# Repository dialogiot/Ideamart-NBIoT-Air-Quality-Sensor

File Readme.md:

##  Ideamart NB-IoT Air Quality Sensor

The board is developed based on the SIM7000C and SIM7000E Modules as well as the Microcontroller ATMega 328 based on the most popular Arduino UNO PIN layout. Therefore this board is compatible with any shield that is compatible with the Arduino UNO

* Temperature(Celsius)
* Carbon Dioxide(ppm)
* Pressure(Pa)
* Humidity(%)
* Ammonia(ppm)
* Butane(ppm)
* Carbon Monoxide(ppm)
* Ethanol(ppm)
* Hydrogen(ppm)
* Methane(ppm)
* Nitrogen Dioxide(ppm)
* Propane(ppm)
* Latitude, Longitude
* Altitude(m)
* MSL Altitude(m)
* Speed Over Ground(km/h)
* Course Over Ground(degrees)
* RSSI
* Battery Level(%)
* UTC date & Time
* Volatile Organic Compound(ppb)

More  (https://idealab.ideamart.io/EnvSensor/)

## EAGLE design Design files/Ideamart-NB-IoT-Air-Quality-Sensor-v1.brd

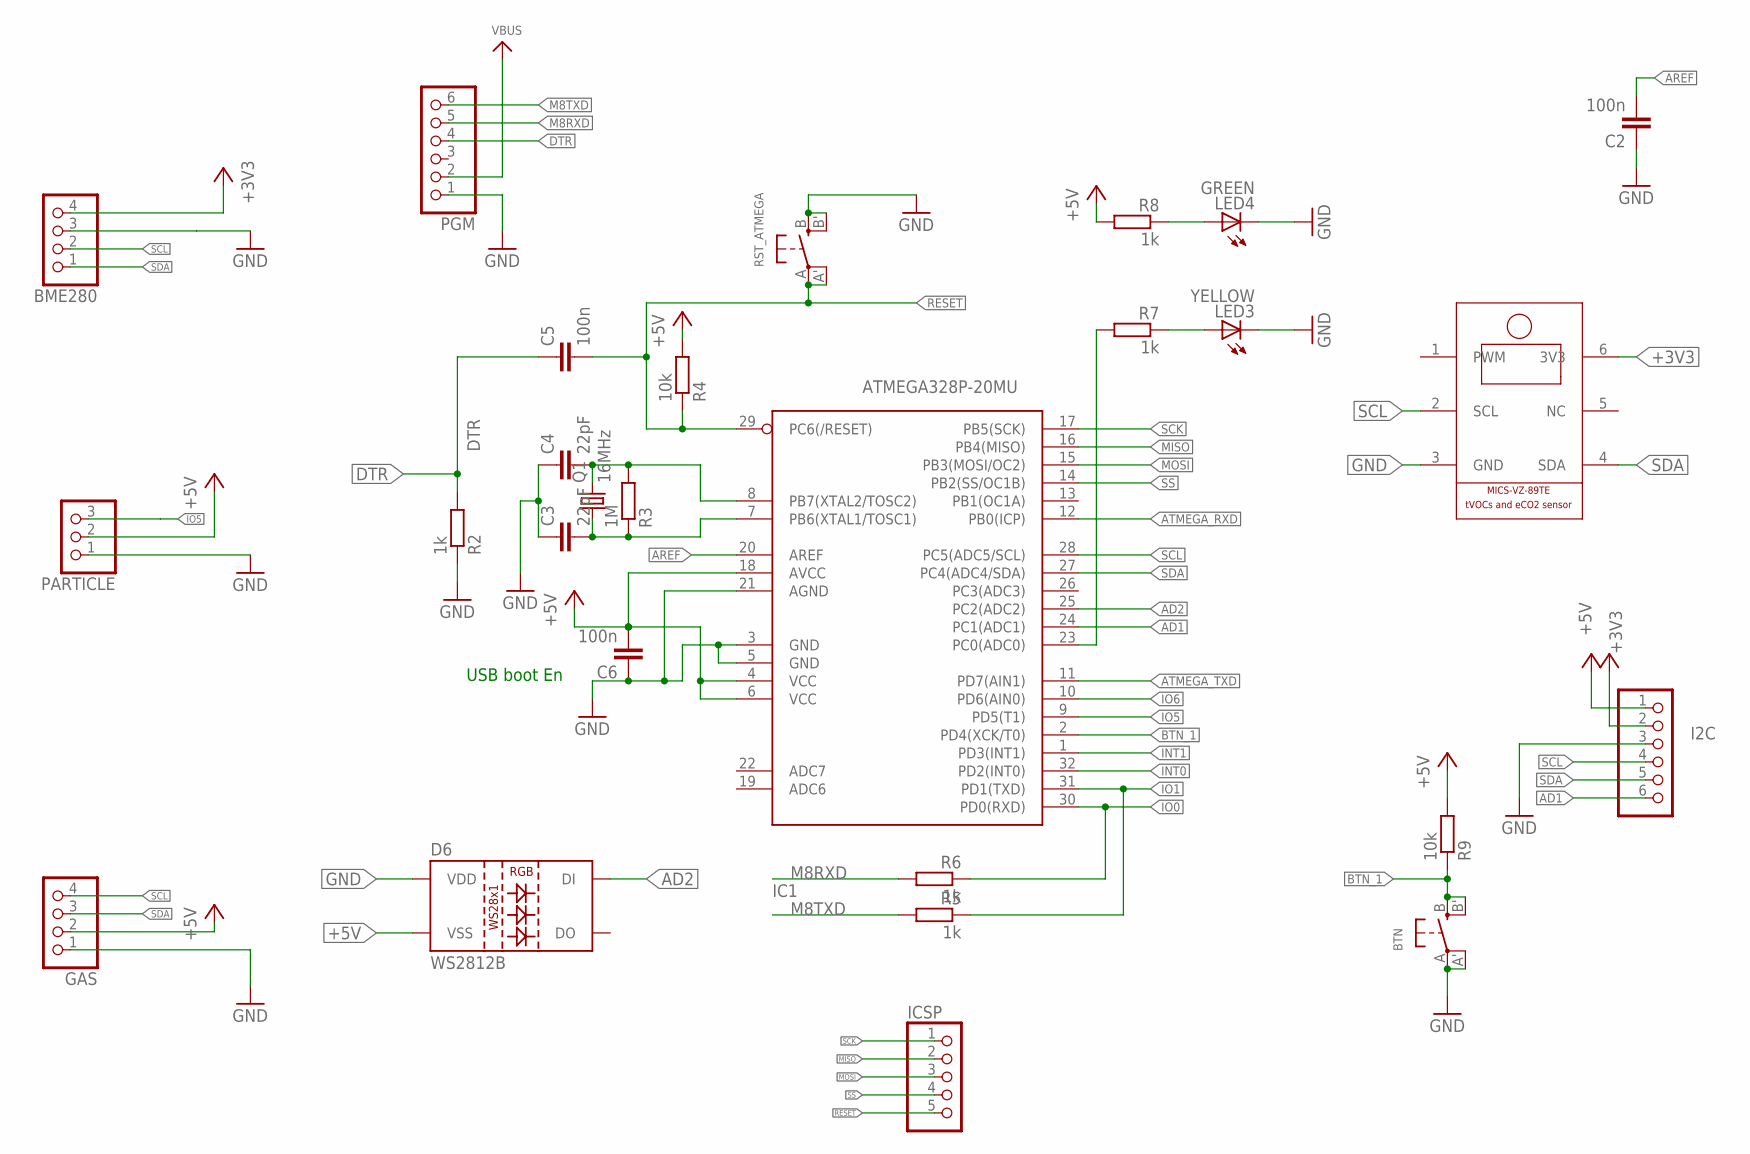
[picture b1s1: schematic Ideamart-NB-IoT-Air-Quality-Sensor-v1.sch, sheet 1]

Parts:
BME280: PINHD-1X4; 1X04
BTN: SWITCH_TACT_SMT4.6X2.8; BTN_KMR2_4.6X2.8
C2, C5, C6: 100n; C0805
C3, C4: 22pF; C0805
D6: WS2812B
GAS: PINHD-1X4; 1X04
I2C: PINHD-1X6; 1X06
IC1: ATMEGA328P-20MU; TQFP32-08
ICSP: PINHD-1X5; 1X05
LED3: YELLOW; CHIP-LED0805
LED4: GREEN; CHIP-LED0805
PARTICLE: PINHD-1X3; 1X03
PGM: PINHD-1X6; 1X06
Q1: 16MHz; CTS406
R2, R5, R6, R7, R8: 1k; R0805
R3: 1M; R0805
R4, R9: 10k; R0805
RST_ATMEGA: SWITCH_TACT_SMT4.6X2.8; BTN_KMR2_4.6X2.8
U$1: MICS-VZ-89TE

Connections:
+3V3: BME280.4, I2C.2, U$1.6 (3V3); also elsewhere on the board
+5V: C6.2, D6.3 (VSS), GAS.2, I2C.1, IC1.4 (VCC), IC1.6 (VCC), IC1.18 (AVCC), PARTICLE.2, R4.2, R8.2, R9.2; also elsewhere on the board
AD1: I2C.6, IC1.24 (PC1(ADC1))
AD2: D6.4 (DI), IC1.25 (PC2(ADC2))
AREF: C2.2, IC1.20 (AREF)
ATMEGA_RXD: IC1.12 (PB0(ICP)); also elsewhere on the board
ATMEGA_TXD: IC1.11 (PD7(AIN1)); also elsewhere on the board
BTN_1: BTN.B (S), BTN.B' (S1), IC1.2 (PD4(XCK/T0)), R9.1
DTR: C5.1, PGM.4, R2.2
GND: BME280.3, BTN.A, BTN.A' (P1), C2.1, C3.1, C4.1, C6.1, D6.1 (VDD), GAS.1, I2C.3, IC1.3 (GND), IC1.5 (GND), IC1.21 (AGND), LED3.C, LED4.C, PARTICLE.1, PGM.1, R2.1, RST_ATMEGA.B (S), RST_ATMEGA.B' (S1), U$1.3 (GND); also elsewhere on the board
INT0: IC1.32 (PD2(INT0))
INT1: IC1.1 (PD3(INT1))
IO0: IC1.30 (PD0(RXD)), R6.1
IO1: IC1.31 (PD1(TXD)), R5.1
IO5: IC1.9 (PD5(T1)), PARTICLE.3
IO6: IC1.10 (PD6(AIN0))
M8RXD: PGM.5, R6.2
M8TXD: PGM.6, R5.2
MISO: IC1.16 (PB4(MISO)), ICSP.2
MOSI: IC1.15 (PB3(MOSI/OC2)), ICSP.3; also elsewhere on the board
unnamed: LED3.A, R7.1
unnamed: LED4.A, R8.1
unnamed: IC1.23 (PC0(ADC0)), R7.2
RESET: C5.2, IC1.29 (PC6(/RESET)), ICSP.5, R4.1, RST_ATMEGA.A, RST_ATMEGA.A' (P1)
SCK: IC1.17 (PB5(SCK)), ICSP.1; also elsewhere on the board
SCL: BME280.2, GAS.4, I2C.4, IC1.28 (PC5(ADC5/SCL)), U$1.2 (SCL)
SDA: BME280.1, GAS.3, I2C.5, IC1.27 (PC4(ADC4/SDA)), U$1.4 (SDA)
SS: IC1.14 (PB2(SS/OC1B)), ICSP.4
VBUS: PGM.2; also elsewhere on the board
XTAL1: C3.2, IC1.7 (PB6(XTAL1/TOSC1)), Q1.1, R3.1
XTAL2: C4.2, IC1.8 (PB7(XTAL2/TOSC2)), Q1.3 (2), R3.2

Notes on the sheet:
USB boot En

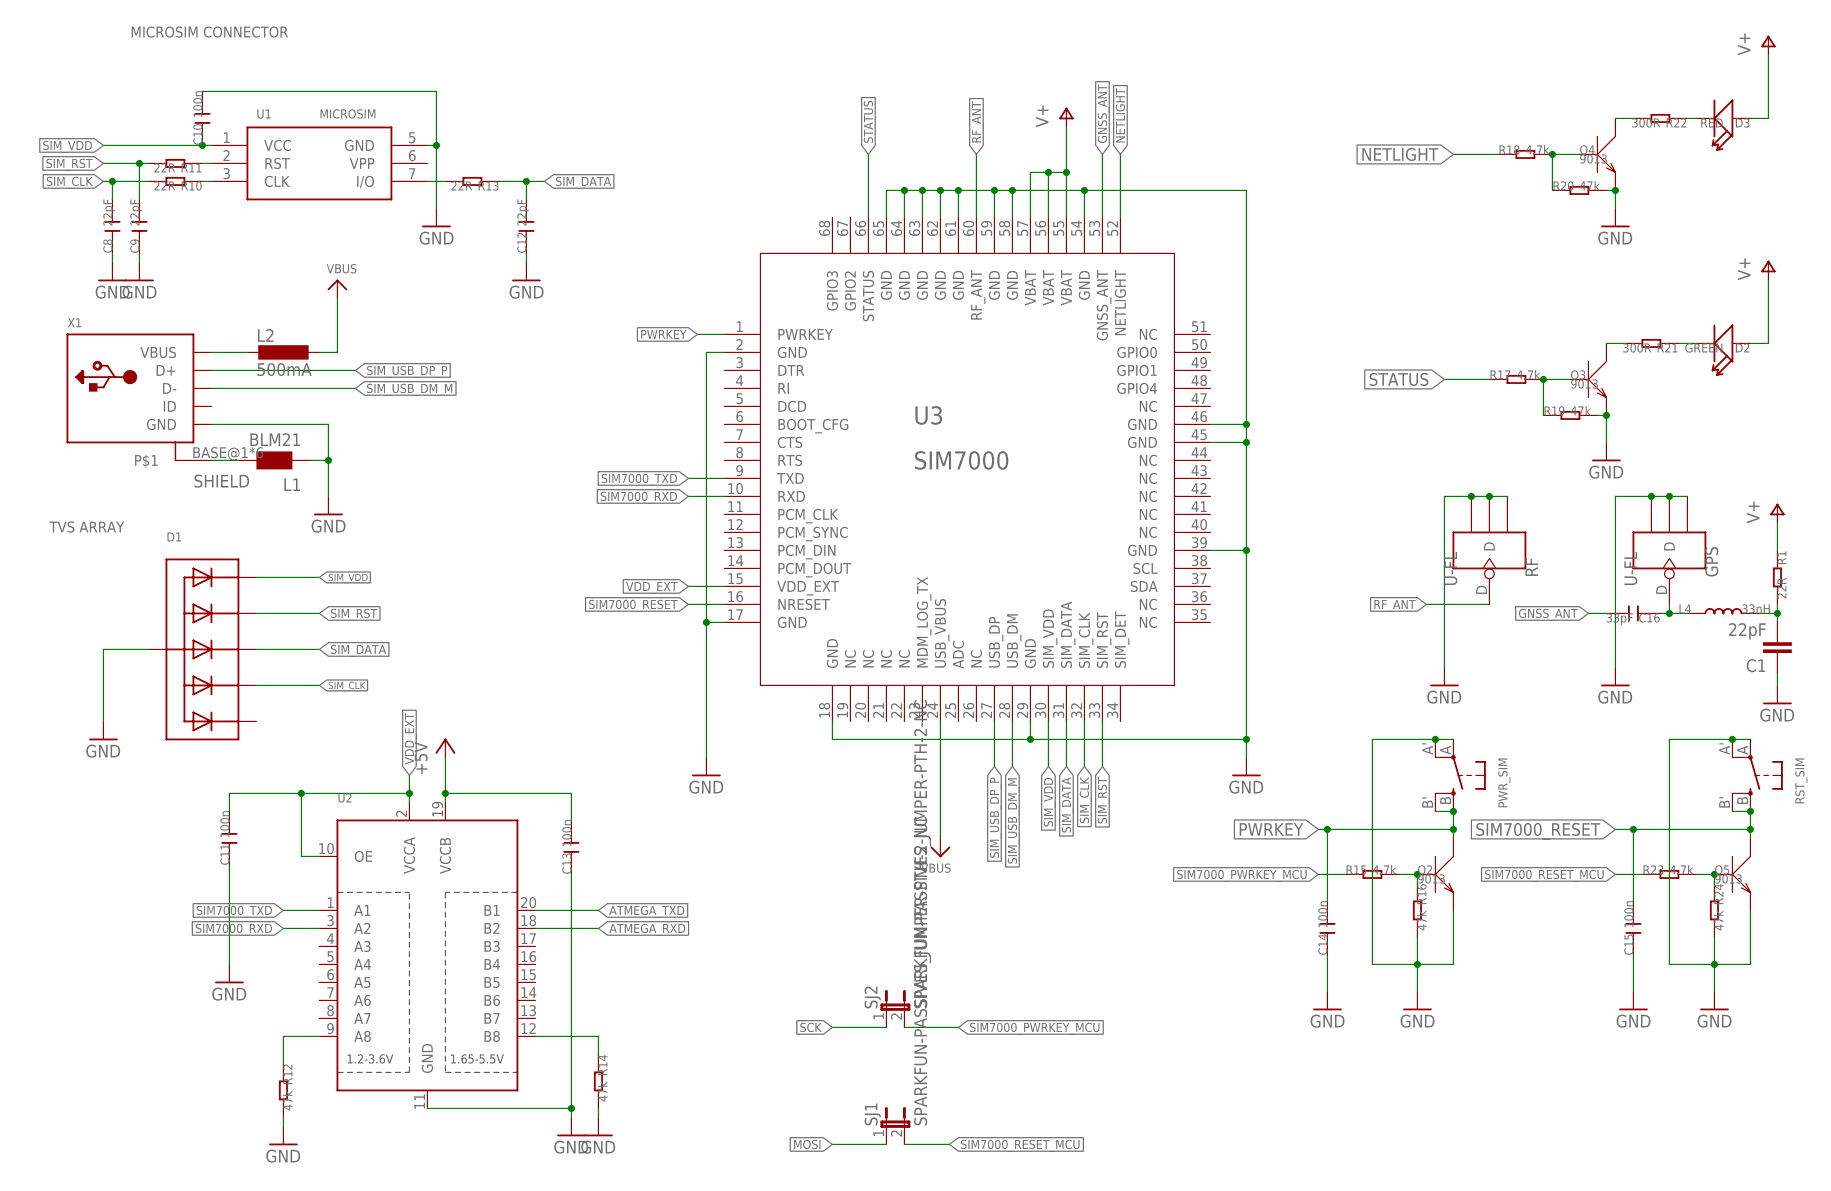
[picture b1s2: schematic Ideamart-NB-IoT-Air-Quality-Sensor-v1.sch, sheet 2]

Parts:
C1: 22pF; C0805
C8, C9, C12: 22pF; 0805
C10, C11, C13, C14, C15: 100n; 0805
C16: 33pF; 0805
D1: TVSARRAY_5LANE; SOT363
D2: GREEN; LED-0805
D3: RED; LED-0805
GPS: U-FL; 4P-U-FL
L1: BLM21; 0805
L2: 500mA; L1812
L4: 33nH; L0805
PWR_SIM: SWITCH_TACT_SMT4.6X2.8; BTN_KMR2_4.6X2.8
Q2, Q3, Q4, Q5: 9013; SOT23
R1, R10, R11, R13: 22R; 0805
R12, R14, R16, R19, R20, R24: 47k; 0805
R15, R17, R18, R23: 4.7k; 0805
R21, R22: 300R; 0805
RF: U-FL; 4P-U-FL
RST_SIM: SWITCH_TACT_SMT4.6X2.8; BTN_KMR2_4.6X2.8
SJ1, SJ2: SPARKFUN-PASSIVES_JUMPER-PTH-2-NC; SPARKFUN-PASSIVES_PTH-JUMPER-NC_BOTTOM_NO_SILK
U1: MICROSIM
U2: TXB0108PWR; TSSOP20
U3: SIM7000
X1: USB_MICRO_20329_V2; 4UCONN_20329_V2

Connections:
+5V: C13.2, U2.19 (VCCB); also elsewhere on the board
ATMEGA_RXD: U2.18 (B2); also elsewhere on the board
ATMEGA_TXD: U2.20 (B1); also elsewhere on the board
GND: C1.1, C8.1, C9.1, C10.2, C11.1, C12.1, C13.1, C14.1, C15.1, D1.2 (A), GPS.GND1, GPS.GND2, GPS.GND3, L1.1, PWR_SIM.A, PWR_SIM.A' (P1), Q2.2 (E), Q3.2 (E), Q4.2 (E), Q5.2 (E), R12.2, R14.2, R16.2, R19.2, R20.2, R24.2, RF.GND1, RF.GND2, RF.GND3, RST_SIM.A, RST_SIM.A' (P1), U1.5 (GND), U2.11 (GND), U3.2 (GND), U3.17 (GND), U3.18 (GND), U3.29 (GND), U3.39 (GND), U3.45 (GND), U3.46 (GND), U3.54 (GND), U3.58 (GND), U3.59 (GND), U3.61 (GND), U3.62 (GND), U3.63 (GND), U3.64 (GND), U3.65 (GND), X1.GND; also elsewhere on the board
GNSS_ANT: C16.2, U3.53 (GNSS_ANT)
GPIO2: U3.67 (GPIO2)
GPIO3: U3.68 (GPIO3)
MOSI: SJ1.1; also elsewhere on the board
unnamed: Q3.3 (C), R21.2
unnamed: D2.-, R21.1
unnamed: Q3.1 (B), R17.2, R19.1
unnamed: R13.2, U1.7 (I/O)
unnamed: R10.1, U1.3 (CLK)
unnamed: R11.1, U1.2 (RST)
unnamed: Q5.1 (B), R23.2, R24.1
unnamed: L2.2, X1.VBUS
unnamed: Q4.3 (C), R22.2
unnamed: D3.-, R22.1
unnamed: Q4.1 (B), R18.2, R20.1
unnamed: C16.1, GPS.D, L4.1
unnamed: R12.1, U2.9 (A8)
unnamed: R14.1, U2.12 (B8)
unnamed: C1.2, L4.2, R1.2
unnamed: Q2.1 (B), R15.2, R16.1
NETLIGHT: R18.1, U3.52 (NETLIGHT)
PWRKEY: C14.2, PWR_SIM.B (S), PWR_SIM.B' (S1), Q2.3 (C), U3.1 (PWRKEY)
RF_ANT: RF.D, U3.60 (RF_ANT)
SCK: SJ2.1; also elsewhere on the board
SHIELD: L1.2, X1.BASE@1, X1.BASE@2, X1.SPRT@1, X1.SPRT@2, X1.SPRT@3, X1.SPRT@4
SIM7000_PWRKEY_MCU: R15.1, SJ2.2
SIM7000_RESET: C15.2, Q5.3 (C), RST_SIM.B (S), RST_SIM.B' (S1), U3.16 (NRESET)
SIM7000_RESET_MCU: R23.1, SJ1.2
SIM7000_RXD: U2.3 (A2), U3.10 (RXD)
SIM7000_TXD: U2.1 (A1), U3.9 (TXD)
SIM_CLK: C8.2, D1.5 (C4), R10.2, U3.32 (SIM_CLK)
SIM_DATA: C12.2, D1.4 (C3), R13.1, U3.31 (SIM_DATA)
SIM_RST: C9.2, D1.3 (C2), R11.2, U3.33 (SIM_RST)
SIM_USB_DM_M: U3.28 (USB_DM), X1.D-
SIM_USB_DP_P: U3.27 (USB_DP), X1.D+
SIM_VDD: C10.1, D1.1 (C1), U1.1 (VCC), U3.30 (SIM_VDD)
STATUS: R17.1, U3.66 (STATUS)
V+: D2.+, D3.+, R1.1, U3.55 (VBAT), U3.56 (VBAT), U3.57 (VBAT); also elsewhere on the board
VBUS: L2.1, U3.24 (USB_VBUS); also elsewhere on the board
VDD_EXT: C11.2, U2.2 (VCCA), U2.10 (OE), U3.15 (VDD_EXT)

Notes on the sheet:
TVS ARRAY
MICROSIM CONNECTOR

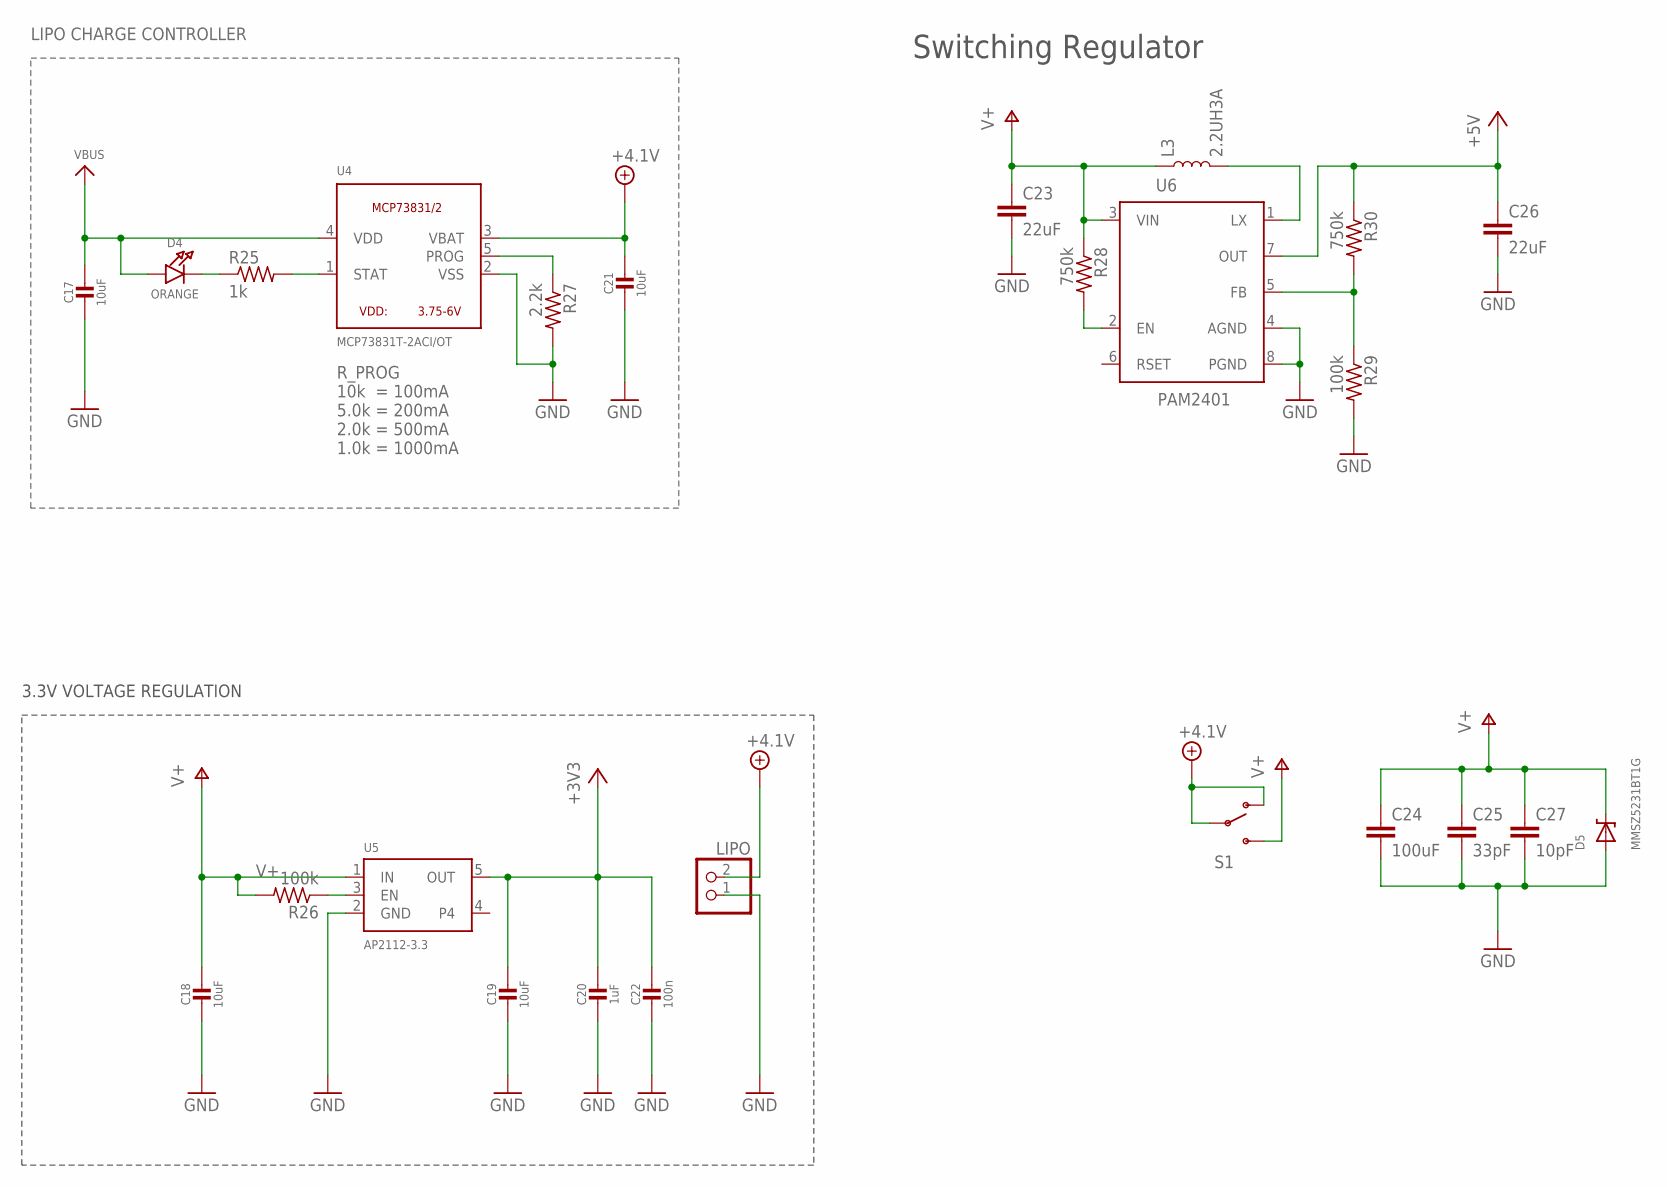
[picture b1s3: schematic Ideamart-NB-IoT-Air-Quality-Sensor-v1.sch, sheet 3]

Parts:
C17, C21: 10uF; _0805
C18, C19: 10uF; _0805MP
C20: 1uF; _0805MP
C22: 100n; _0805MP
C23, C26: 22uF; 0805
C24: 100uF; 1210
C25: 33pF; 0805
C27: 10pF; 0805
D4: ORANGE; CHIPLED_0805
D5: MMSZ5231BT1G; SOD-123
L3: 2.2UH3A; INDUCTOR_4X4MM
LIPO: JST_2PIN-SMT; JST-PH-2-SMT
R25: 1k; M0805
R26, R29: 100k; M0805
R27: 2.2k; M0805
R28, R30: 750k; M0805
S1: SWITCH-SPDT-SMD-A; SWITCH-SPST-SMD-A
U4: MCP73831T-2ACI/OT; SOT23-5
U5: AP2112-3.3; SOT23-5
U6: PAM2401; MSOP8

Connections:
+3V3: C19.1, C20.1, C22.1, U5.5 (OUT); also elsewhere on the board
+4.1V: C21.1, LIPO.2 (1), S1.1 (O), S1.2, U4.3 (VBAT)
+5V: C26.1, R30.1, U6.7 (OUT); also elsewhere on the board
EN: R28.2, U6.2 (EN)
GND: C17.2, C18.2, C19.2, C20.2, C21.2, C22.2, C23.2, C24.2, C25.2, C26.2, C27.2, D5.A, LIPO.1 (2), R27.2, R29.2, U4.2 (VSS), U5.2 (GND), U6.4 (AGND), U6.8 (PGND); also elsewhere on the board
unnamed: R26.1, U5.3 (EN)
unnamed: D4.C, R25.1
unnamed: R25.2, U4.1 (STAT)
unnamed: R27.1, U4.5 (PROG)
unnamed: R29.1, R30.2, U6.5 (FB)
unnamed: L3.P$2 (2), U6.1 (LX)
V+: C18.1, C23.1, C24.1, C25.1, C27.1, D5.C, L3.P$1 (1), R26.2, R28.1, S1.3 (S), U5.1 (IN), U6.3 (VIN); also elsewhere on the board
VBUS: C17.1, D4.A, U4.4 (VDD); also elsewhere on the board

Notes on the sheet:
3.3V VOLTAGE REGULATION
R_PROG 10k = 100mA 5.0k = 200mA 2.0k = 500mA 1.0k = 1000mA
LIPO CHARGE CONTROLLER
Switching Regulator

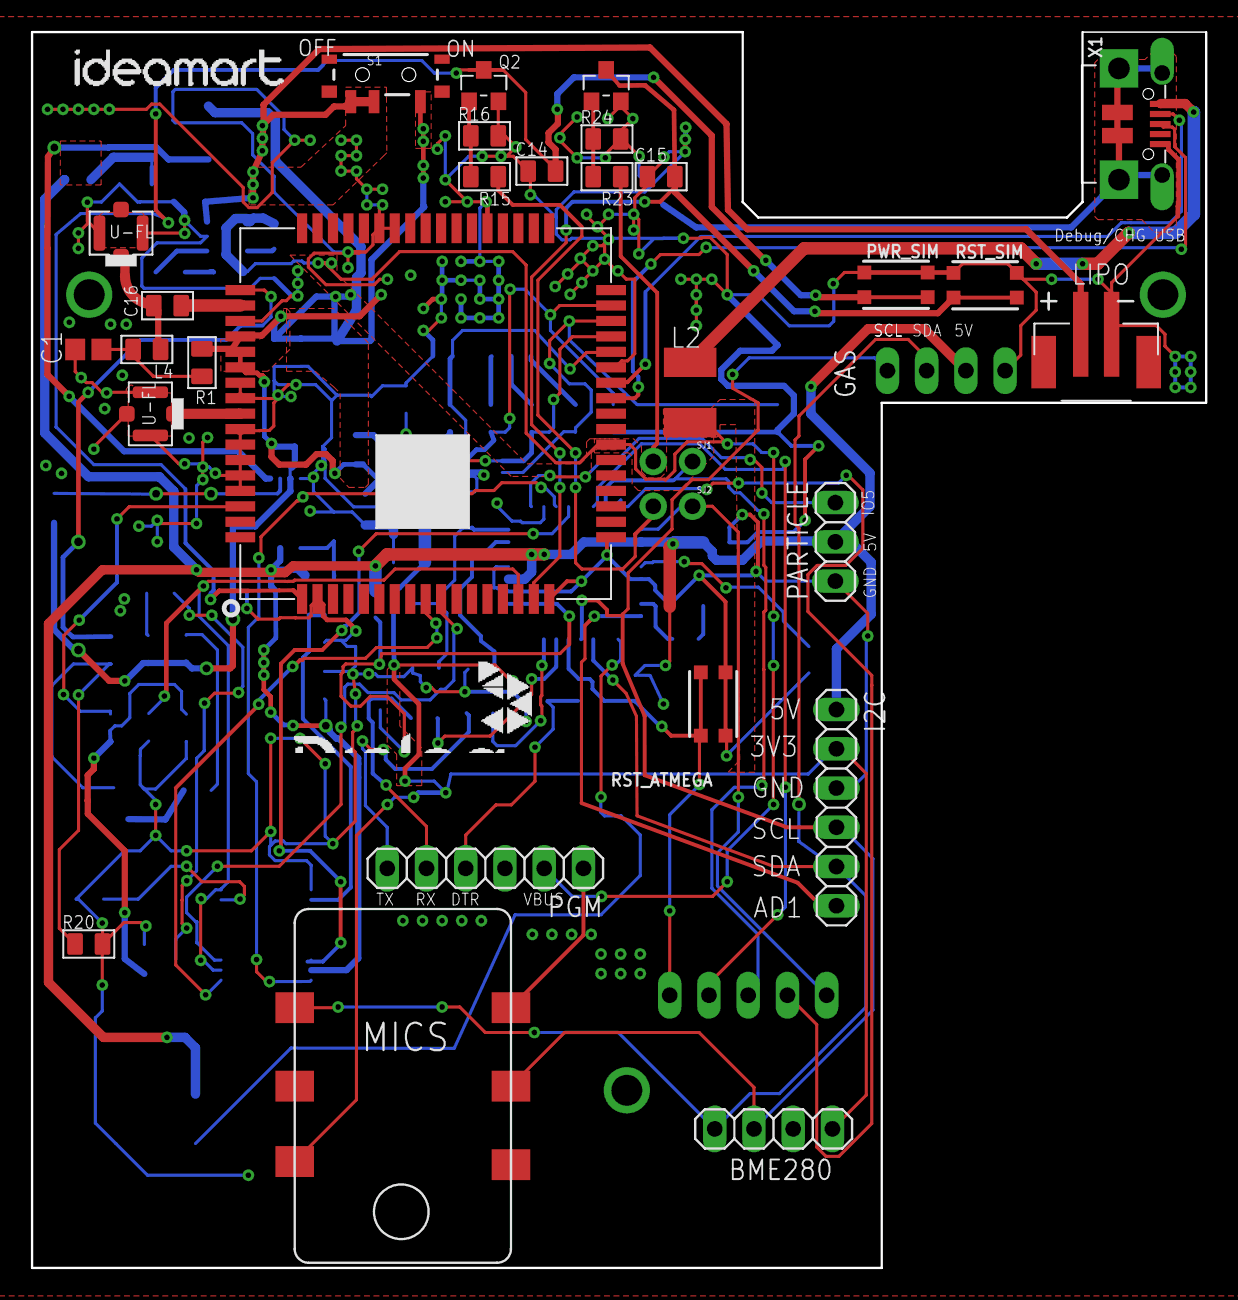
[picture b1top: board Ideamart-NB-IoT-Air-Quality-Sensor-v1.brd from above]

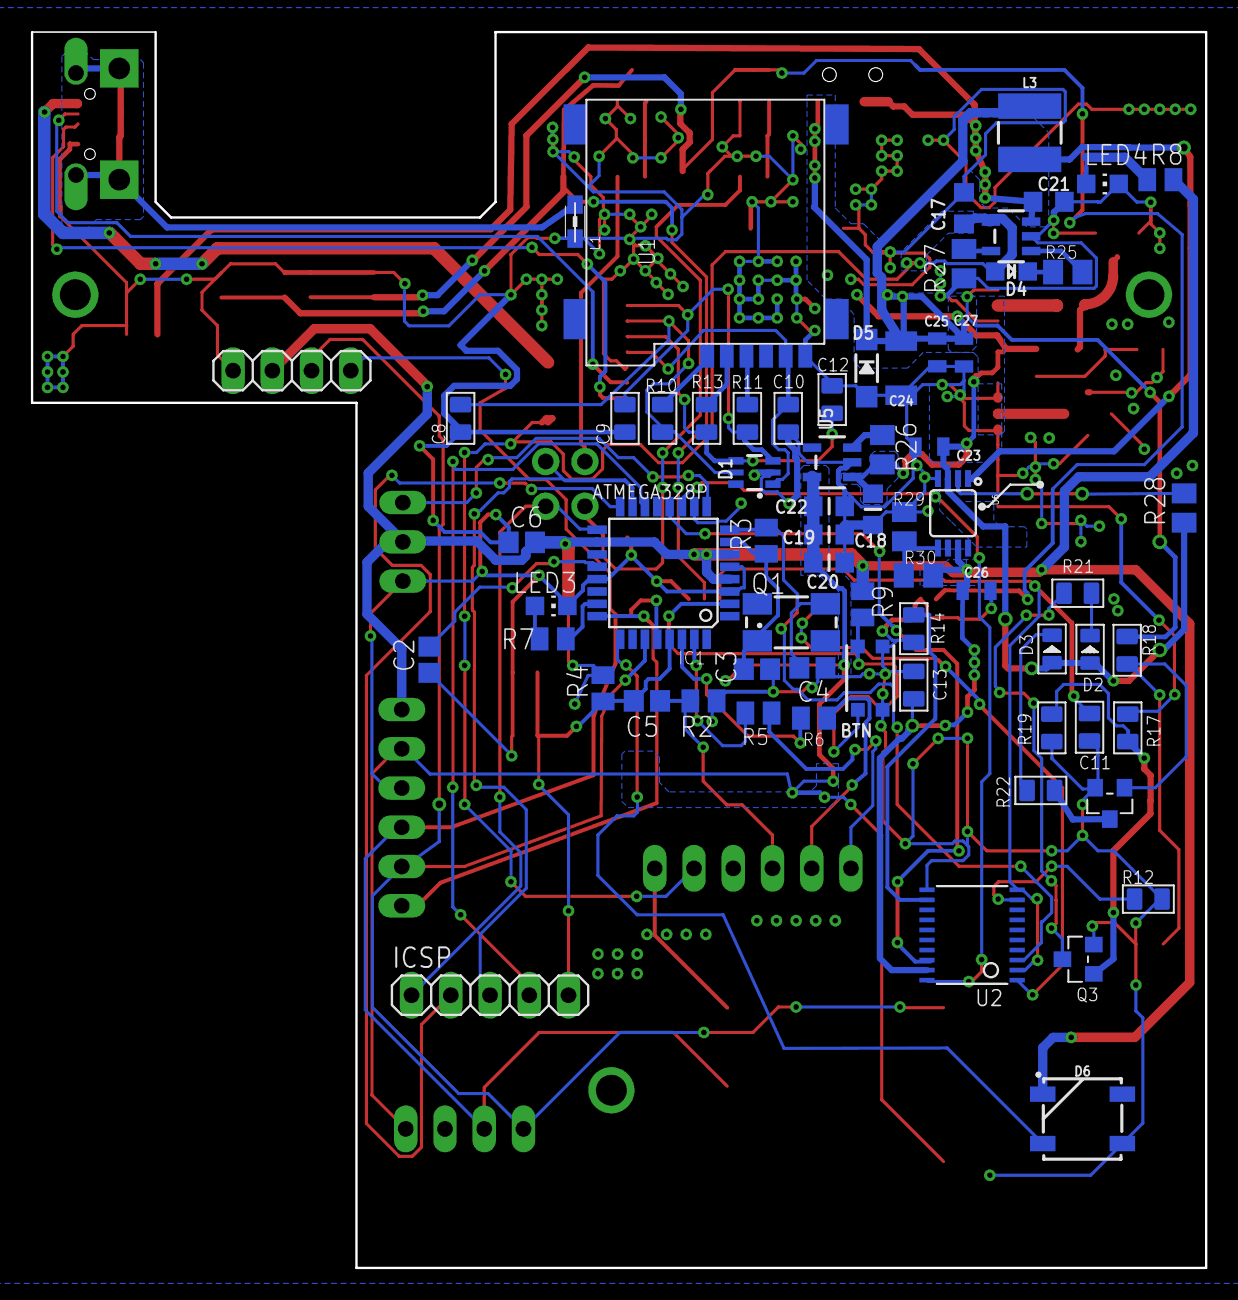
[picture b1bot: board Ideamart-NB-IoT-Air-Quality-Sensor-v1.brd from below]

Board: 2 copper layers, 76.0 x 80.0 mm, 98 parts (68 on the bottom side), 71 nets.

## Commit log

2019-01-18 Add files via upload
    Eagle design files for Air quality sensor version 1
2019-01-18 Add files via upload
    Arduino code for Air quality measurements

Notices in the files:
parts and their libraries:
SparkFun-Capacitors: Licensing: CC v3.0 Share-Alike You are welcome to use this library for commercial purposes.
SparkFun-Coils: Licensing: Creative Commons ShareAlike 4.0 International - https://creativecommons.org/licenses/by-sa/4.0
